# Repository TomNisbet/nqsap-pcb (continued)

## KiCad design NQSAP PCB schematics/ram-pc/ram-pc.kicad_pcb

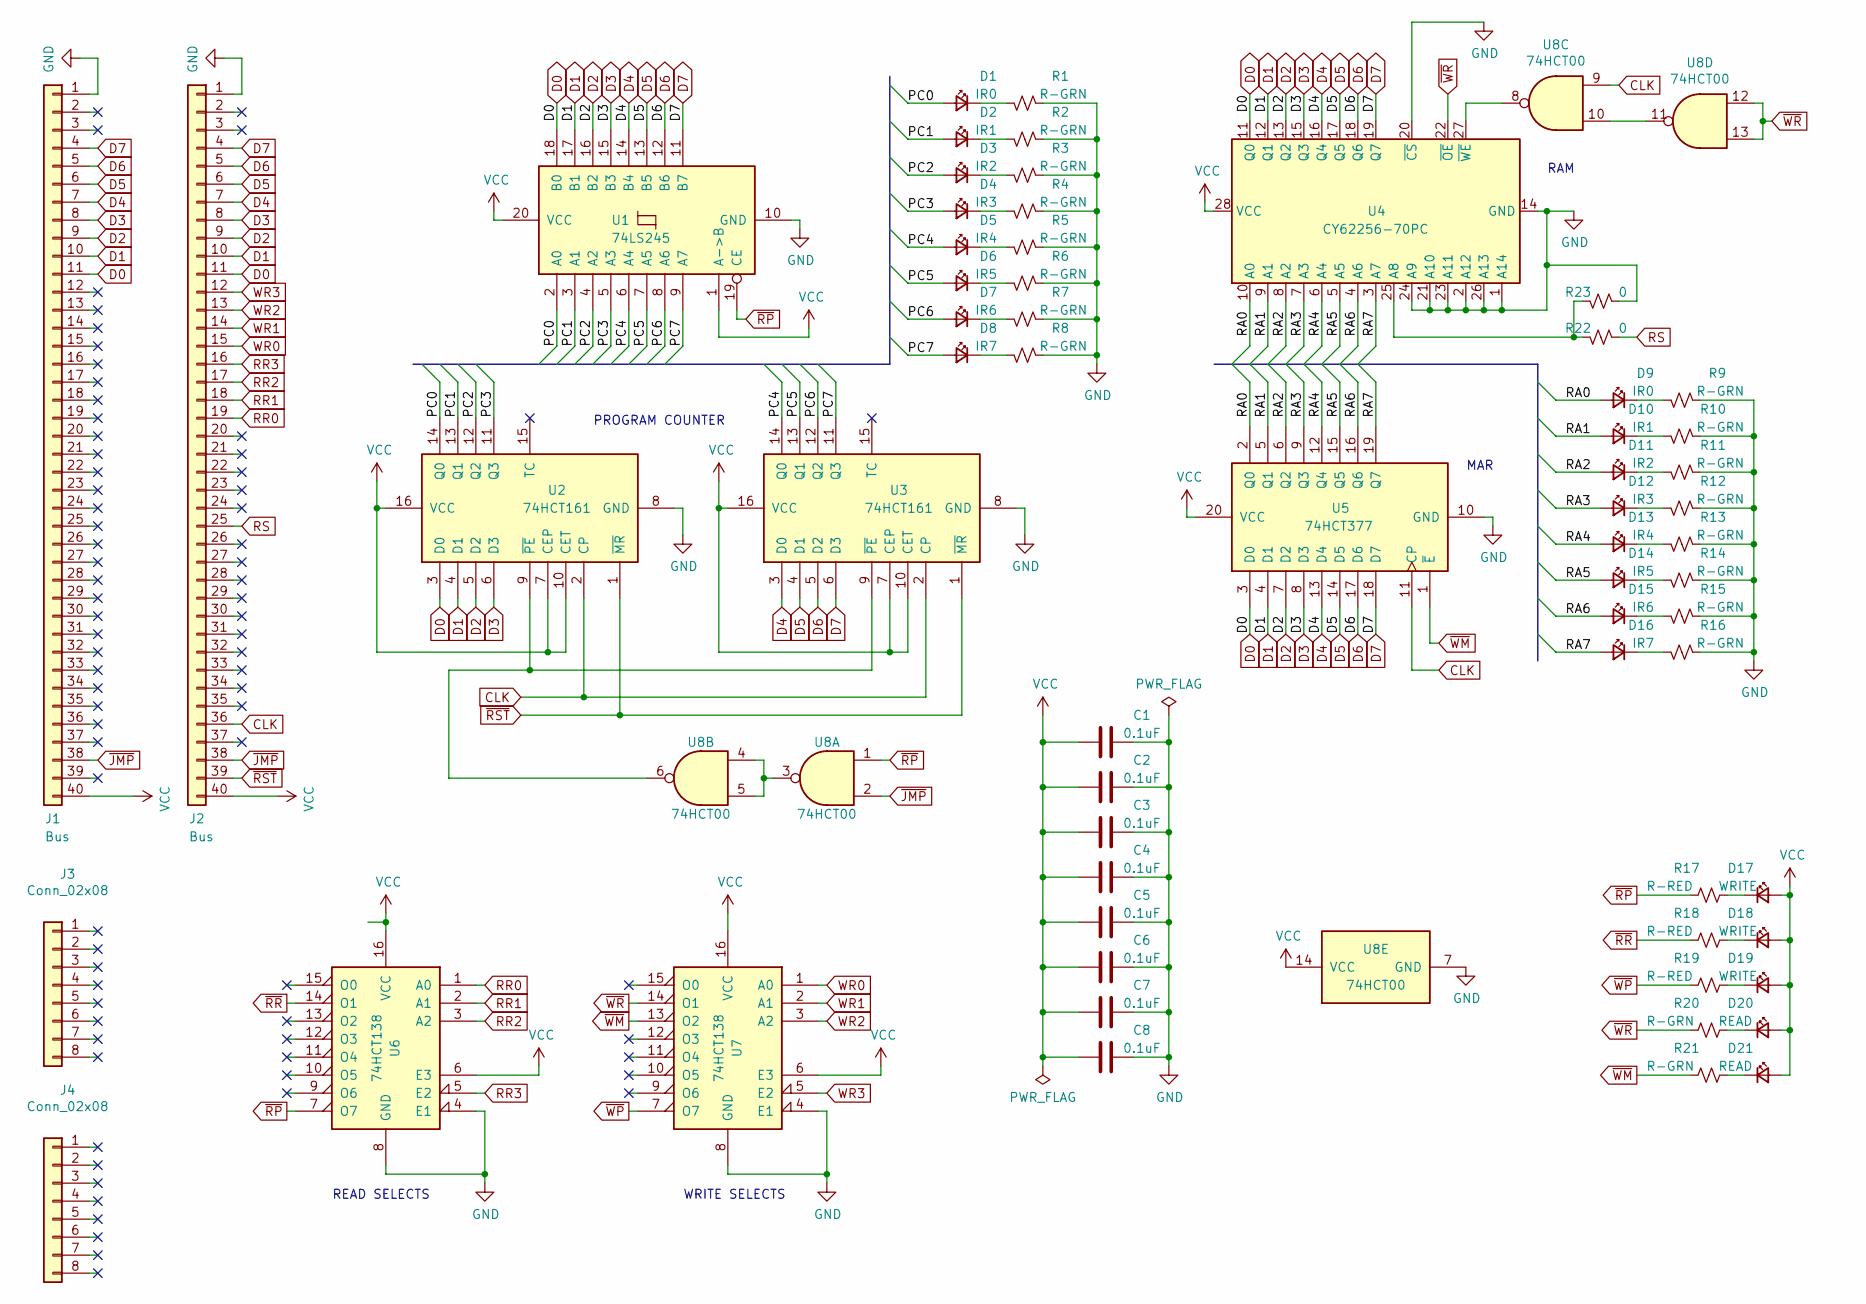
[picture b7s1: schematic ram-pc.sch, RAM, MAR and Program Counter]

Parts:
C1, C2, C3, C4, C5, C6, C7, C8: 0.1uF; C_0805_2012Metric_Pad1.18x1.45mm_HandSolder
D1, D9: IR0; LED_0805_2012Metric_Pad1.15x1.40mm_HandSolder
D2, D10: IR1; LED_0805_2012Metric_Pad1.15x1.40mm_HandSolder
D3, D11: IR2; LED_0805_2012Metric_Pad1.15x1.40mm_HandSolder
D4, D12: IR3; LED_0805_2012Metric_Pad1.15x1.40mm_HandSolder
D5, D13: IR4; LED_0805_2012Metric_Pad1.15x1.40mm_HandSolder
D6, D14: IR5; LED_0805_2012Metric_Pad1.15x1.40mm_HandSolder
D7, D15: IR6; LED_0805_2012Metric_Pad1.15x1.40mm_HandSolder
D8, D16: IR7; LED_0805_2012Metric_Pad1.15x1.40mm_HandSolder
D17, D18, D19: WRITE; LED_0805_2012Metric_Pad1.15x1.40mm_HandSolder
D20, D21: READ; LED_0805_2012Metric_Pad1.15x1.40mm_HandSolder
J1, J2: Bus; PinHeader_1x40_P2.54mm_Vertical
J3, J4: Conn_02x08; PinHeader_1x08_P2.54mm_Vertical
R1, R2, R3, R4, R5, R6, R7, R8, R9, R10, R11, R12, R13, R14, R15, R16, R20, R21: R-GRN; R_0805_2012Metric_Pad1.20x1.40mm_HandSolder
R17, R18, R19: R-RED; R_0805_2012Metric_Pad1.20x1.40mm_HandSolder
R22, R23: 0; R_0805_2012Metric_Pad1.20x1.40mm_HandSolder
U1: 74LS245; DIP-20_W7.62mm
U2, U3: 74HCT161; DIP-16_W7.62mm
U4: CY62256-70PC; DIP-28_W15.24mm
U5: 74HCT377; DIP-20_W7.62mm
U6, U7: 74HCT138; SOIC-20W_7.5x12.8mm_P1.27mm
U8: 74HCT00; SOIC-14_3.9x8.7mm_P1.27mm

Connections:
/PC0: D1.2 (A), U1.2 (A0), U2.14 (Q0)
/PC1: D2.2 (A), U1.3 (A1), U2.13 (Q1)
/PC2: D3.2 (A), U1.4 (A2), U2.12 (Q2)
/PC3: D4.2 (A), U1.5 (A3), U2.11 (Q3)
/PC4: D5.2 (A), U1.6 (A4), U3.14 (Q0)
/PC5: D6.2 (A), U1.7 (A5), U3.13 (Q1)
/PC6: D7.2 (A), U1.8 (A6), U3.12 (Q2)
/PC7: D8.2 (A), U1.9 (A7), U3.11 (Q3)
/RA0: D9.2 (A), U4.10 (A0), U5.2 (Q0)
/RA1: D10.2 (A), U4.9 (A1), U5.5 (Q1)
/RA2: D11.2 (A), U4.8 (A2), U5.6 (Q2)
/RA3: D12.2 (A), U4.7 (A3), U5.9 (Q3)
/RA4: D13.2 (A), U4.6 (A4), U5.12 (Q4)
/RA5: D14.2 (A), U4.5 (A5), U5.15 (Q5)
/RA6: D15.2 (A), U4.4 (A6), U5.16 (Q6)
/RA7: D16.2 (A), U4.3 (A7), U5.19 (Q7)
CLK: J2.36, U2.2 (CP), U3.2 (CP), U5.11 (CP), U8.9
D0: J1.11, J2.11, U1.18 (B0), U2.3 (D0), U4.11 (Q0), U5.3 (D0)
D1: J1.10, J2.10, U1.17 (B1), U2.4 (D1), U4.12 (Q1), U5.4 (D1)
D2: J1.9, J2.9, U1.16 (B2), U2.5 (D2), U4.13 (Q2), U5.7 (D2)
D3: J1.8, J2.8, U1.15 (B3), U2.6 (D3), U4.15 (Q3), U5.8 (D3)
D4: J1.7, J2.7, U1.14 (B4), U3.3 (D0), U4.16 (Q4), U5.13 (D4)
D5: J1.6, J2.6, U1.13 (B5), U3.4 (D1), U4.17 (Q5), U5.14 (D5)
D6: J1.5, J2.5, U1.12 (B6), U3.5 (D2), U4.18 (Q6), U5.17 (D6)
D7: J1.4, J2.4, U1.11 (B7), U3.6 (D3), U4.19 (Q7), U5.18 (D7)
GND: C1.1, C2.1, C3.1, C4.1, C5.1, C6.1, C7.1, C8.1, J1.1, J2.1, R1.2, R2.2, R3.2, R4.2, R5.2, R6.2, R7.2, R8.2, R9.2, R10.2, R11.2, R12.2, R13.2, R14.2, R15.2, R16.2, R22.2, U1.10 (GND), U2.8 (GND), U3.8 (GND), U4.1 (A14), U4.2 (A12), U4.14 (GND), U4.20 (~CS), U4.21 (A10), U4.23 (A11), U4.24 (A9), U4.26 (A13), U5.10 (GND), U6.4 (E1), U6.8 (GND), U7.4 (E1), U7.8 (GND), U8.7 (GND)
unnamed: D1.1 (K), R1.1
unnamed: D2.1 (K), R2.1
unnamed: D3.1 (K), R3.1
unnamed: D4.1 (K), R4.1
unnamed: D5.1 (K), R5.1
unnamed: D6.1 (K), R6.1
unnamed: D7.1 (K), R7.1
unnamed: D8.1 (K), R8.1
unnamed: D9.1 (K), R9.1
unnamed: D10.1 (K), R10.1
unnamed: D11.1 (K), R11.1
unnamed: D12.1 (K), R12.1
unnamed: D13.1 (K), R13.1
unnamed: D14.1 (K), R14.1
unnamed: D15.1 (K), R15.1
unnamed: D16.1 (K), R16.1
unnamed: D17.1 (K), R17.1
unnamed: D18.1 (K), R18.1
unnamed: D19.1 (K), R19.1
unnamed: D20.1 (K), R20.1
unnamed: D21.1 (K), R21.1
unnamed: R22.1, R23.1, U4.25 (A8)
unnamed: U2.9 (~PE), U3.9 (~PE), U8.6
unnamed: U4.27 (~WE), U8.8
unnamed: U8.3, U8.4, U8.5
unnamed: U8.10, U8.11
RR0: J2.19, U6.1 (A0)
RR1: J2.18, U6.2 (A1)
RR2: J2.17, U6.3 (A2)
RR3: J2.16, U6.5 (E2)
RS: J2.25, R23.2
VCC: C1.2, C2.2, C3.2, C4.2, C5.2, C6.2, C7.2, C8.2, D17.2 (A), D18.2 (A), D19.2 (A), D20.2 (A), D21.2 (A), J1.40, J2.40, U1.1 (A->B), U1.20 (VCC), U2.7 (CEP), U2.10 (CET), U2.16 (VCC), U3.7 (CEP), U3.10 (CET), U3.16 (VCC), U4.28 (VCC), U5.20 (VCC), U6.6 (E3), U6.16 (VCC), U7.6 (E3), U7.16 (VCC), U8.14 (VCC)
WR0: J2.15, U7.1 (A0)
WR1: J2.14, U7.2 (A1)
WR2: J2.13, U7.3 (A2)
WR3: J2.12, U7.5 (E2)
~JMP: J1.38, J2.38, U8.2
~RP: R17.2, U1.19 (CE), U6.7 (O7), U8.1
~RR: R18.2, U6.14 (O1)
~RST: J2.39, U2.1 (~MR), U3.1 (~MR)
~WM: R21.2, U5.1 (~E), U7.13 (O2)
~WP: R19.2, U7.7 (O7)
~WR: R20.2, U4.22 (~OE), U7.14 (O1), U8.12, U8.13

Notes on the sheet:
MAR
PROGRAM COUNTER
RAM
READ SELECTS
WRITE SELECTS

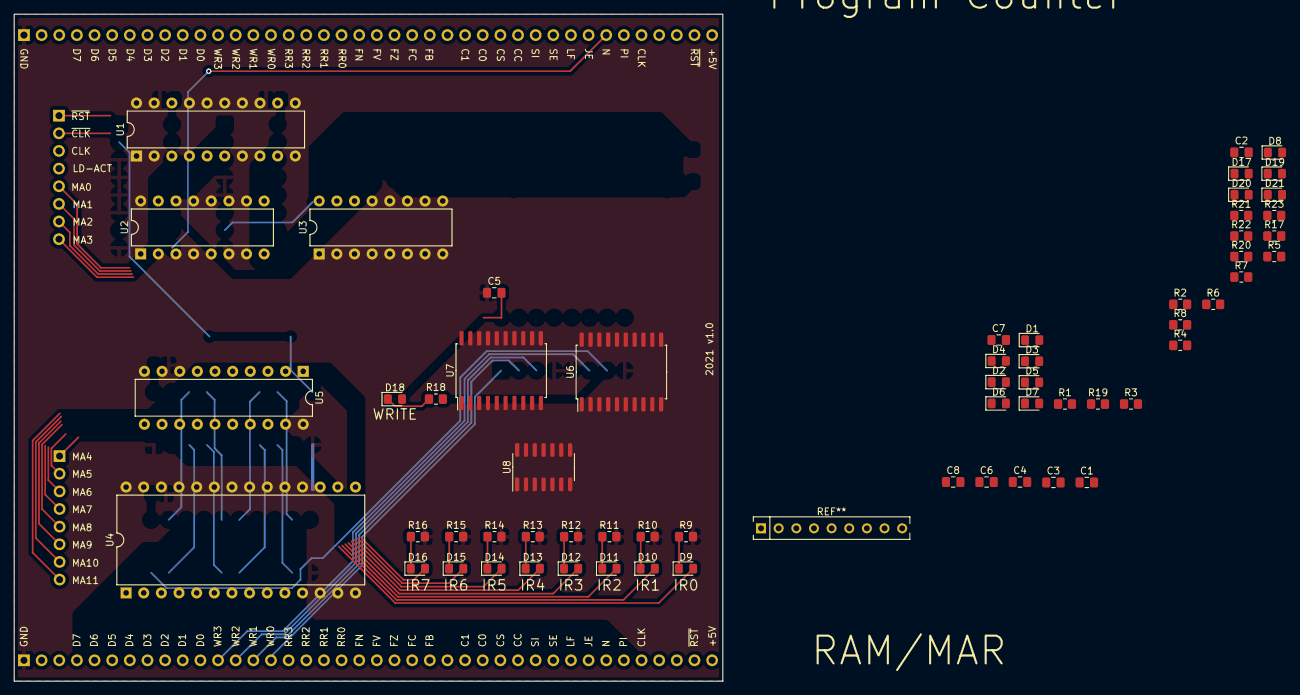
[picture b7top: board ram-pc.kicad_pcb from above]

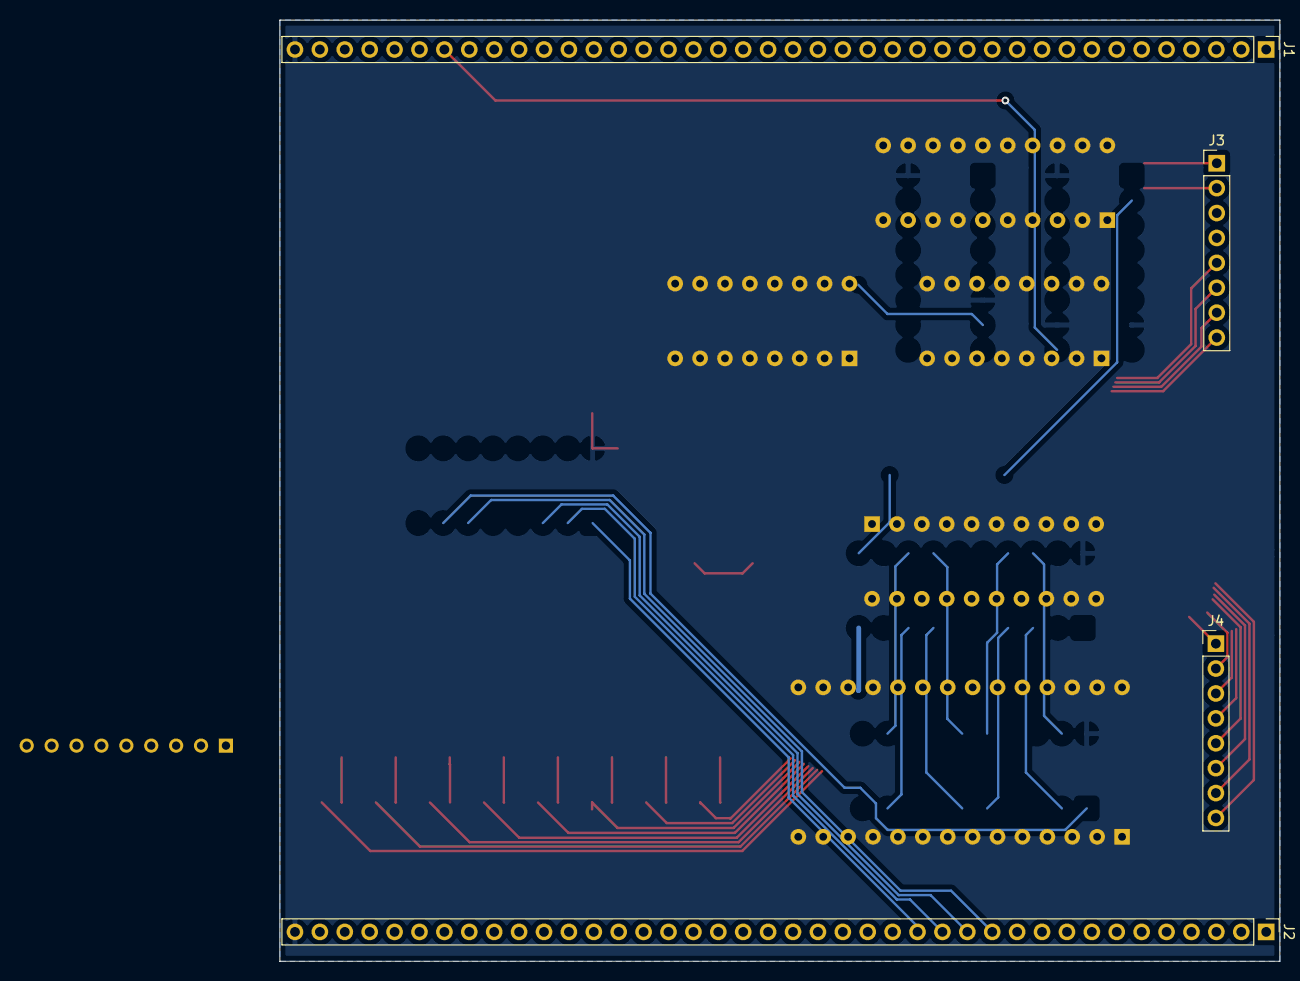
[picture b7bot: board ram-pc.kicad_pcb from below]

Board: 2 copper layers, 102.0 x 96.0 mm, 64 parts (4 on the bottom side), 69 nets.
